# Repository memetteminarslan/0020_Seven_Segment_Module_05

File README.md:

# 0020_Seven_Segment_Module_05
You are seeing a large number of widely used seven segment display modules in electronic development kits. More information coming soon...

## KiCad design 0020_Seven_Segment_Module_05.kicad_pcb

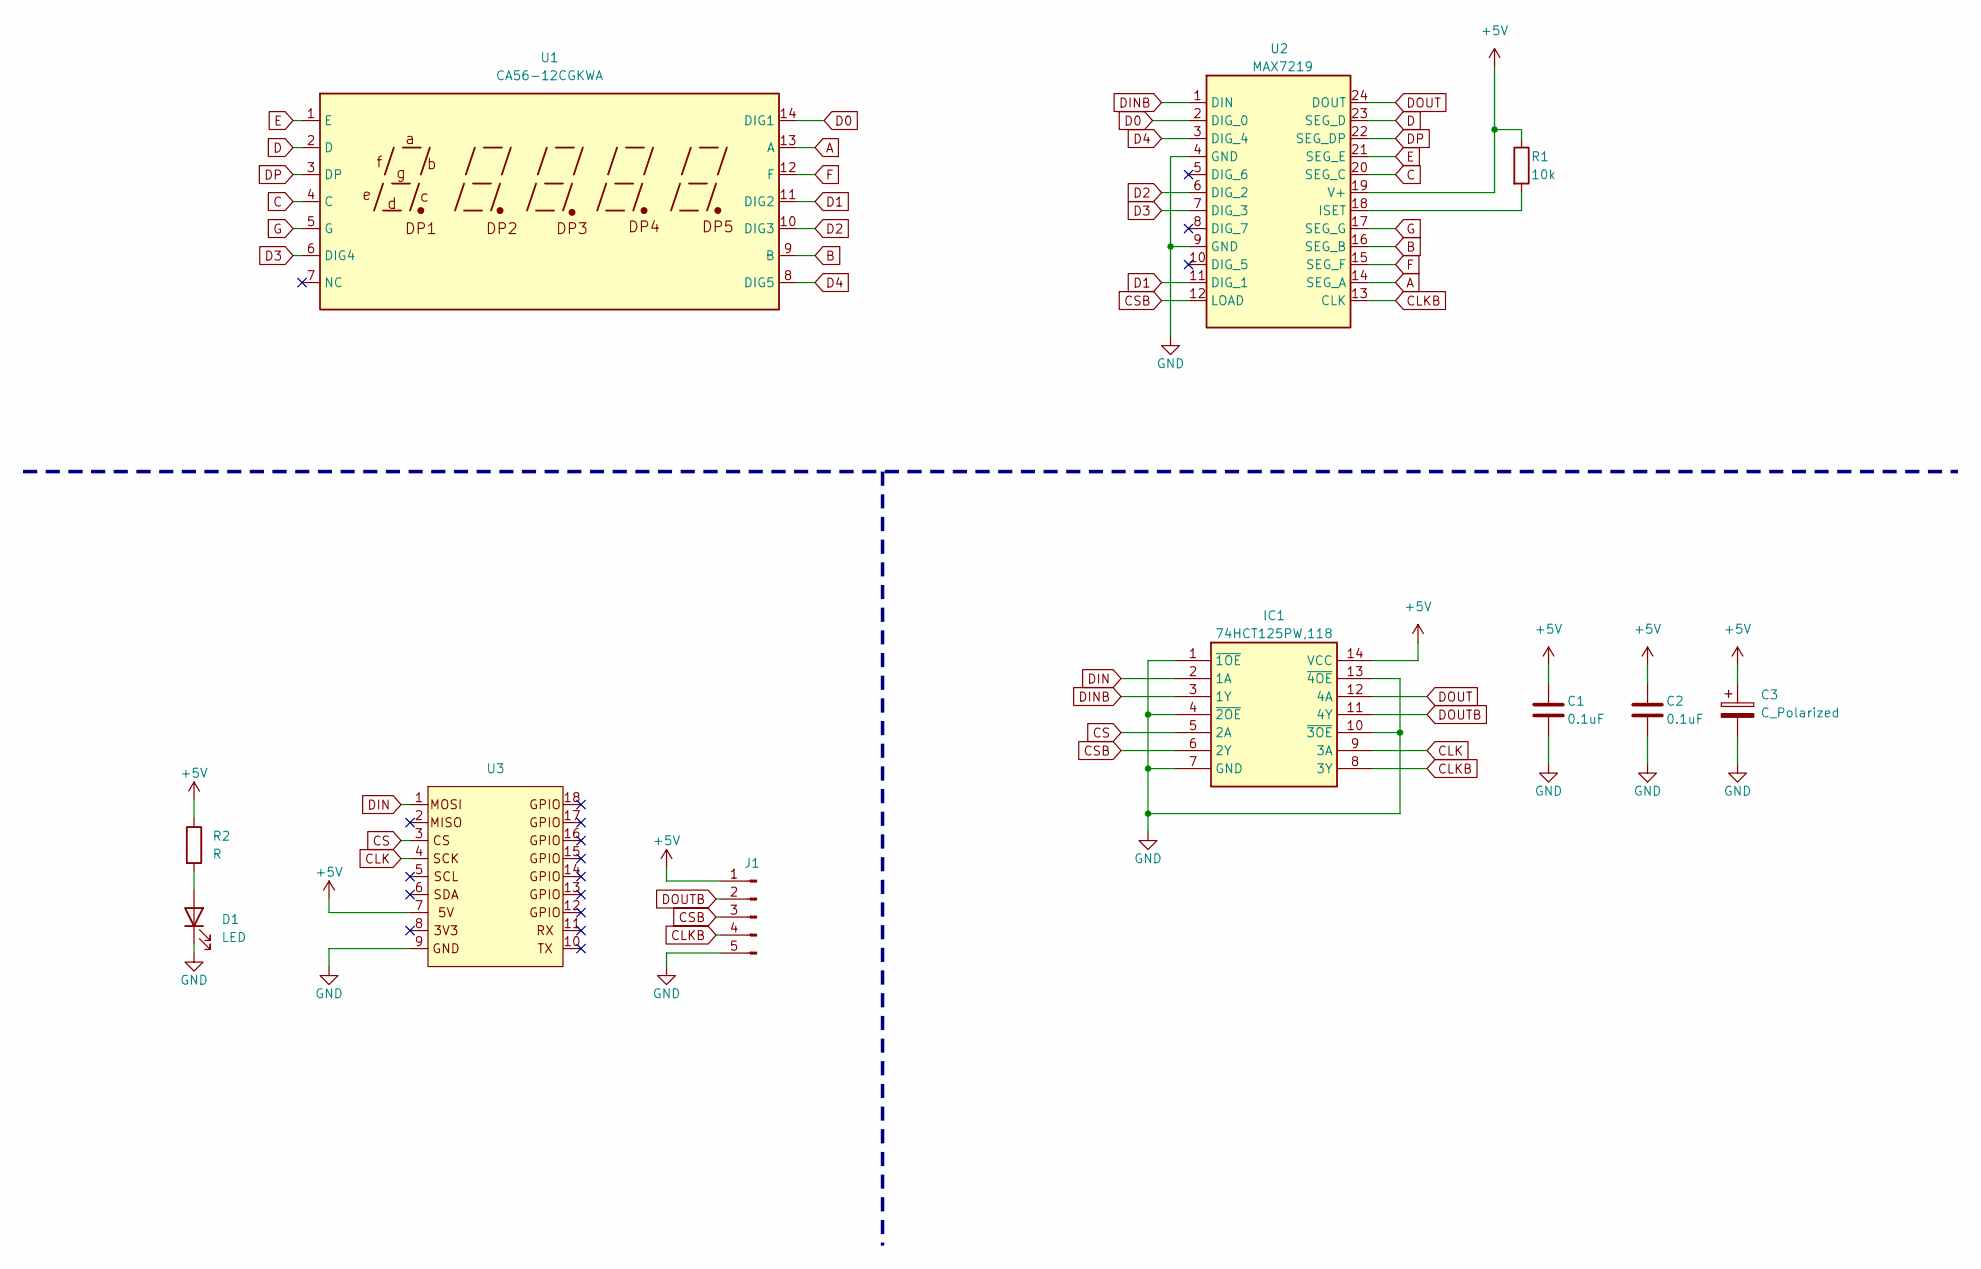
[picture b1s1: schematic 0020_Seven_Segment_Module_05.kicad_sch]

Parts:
C1, C2: 0.1uF; C_0805_2012Metric
C3: C_Polarized; CP_EIA-3216-10_Kemet-I
D1: LED; LED_0603_1608Metric
IC1: 74HCT125PW,118; SOP65P640X110-14N; Mouser Part Number 771-74HCT125PW-T
J1: Conn_01x05_Pin; PinHeader_1x05_P2.54mm_Vertical
R1: 10k; R_0805_2012Metric
R2: R; R_0603_1608Metric
U1: CA56-12CGKWA
U2: MAX7219; SOIC-24W_7.5x15.4mm_P1.27mm
U3: pin_header_5-3

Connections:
+5V: C1.1, C2.1, C3.1, IC1.14 (VCC), J1.1, R1.1, R2.1, U2.19 (V+), U3.7
A: U1.13 (A), U2.14 (SEG_A)
B: U1.9 (B), U2.16 (SEG_B)
C: U1.4 (C), U2.20 (SEG_C)
CLK: IC1.9 (3A), U3.4
CLKB: IC1.8 (3Y), J1.4, U2.13 (CLK)
CS: IC1.5 (2A), U3.3
CSB: IC1.6 (2Y), J1.3, U2.12 (LOAD)
D: U1.2 (D), U2.23 (SEG_D)
D0: U1.14 (DIG1), U2.2 (DIG_0)
D1: U1.11 (DIG2), U2.11 (DIG_1)
D2: U1.10 (DIG3), U2.6 (DIG_2)
D3: U1.6 (DIG4), U2.7 (DIG_3)
D4: U1.8 (DIG5), U2.3 (DIG_4)
DIN: IC1.2 (1A), U3.1
DINB: IC1.3 (1Y), U2.1 (DIN)
DOUT: IC1.12 (4A), U2.24 (DOUT)
DOUTB: IC1.11 (4Y), J1.2
DP: U1.3 (DP), U2.22 (SEG_DP)
E: U1.1 (E), U2.21 (SEG_E)
F: U1.12 (F), U2.15 (SEG_F)
G: U1.5 (G), U2.17 (SEG_G)
GND: C1.2, C2.2, C3.2, D1.1 (K), IC1.1 (~1OE), IC1.4 (~2OE), IC1.7 (GND), IC1.10 (~3OE), IC1.13 (~4OE), J1.5, U2.4 (GND), U2.9 (GND), U3.9
unnamed: D1.2 (A), R2.2
unnamed: R1.2, U2.18 (ISET)

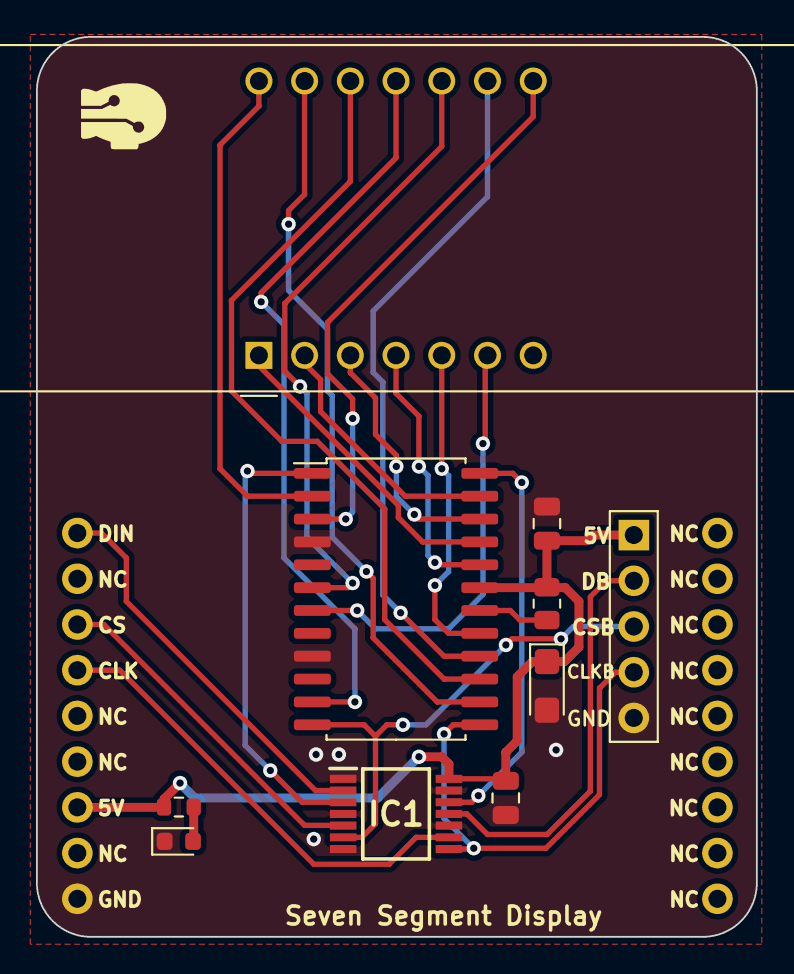
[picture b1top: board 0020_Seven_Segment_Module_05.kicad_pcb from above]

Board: 2 copper layers, 40.0 x 50.0 mm, 11 parts (0 on the bottom side), 25 nets.
